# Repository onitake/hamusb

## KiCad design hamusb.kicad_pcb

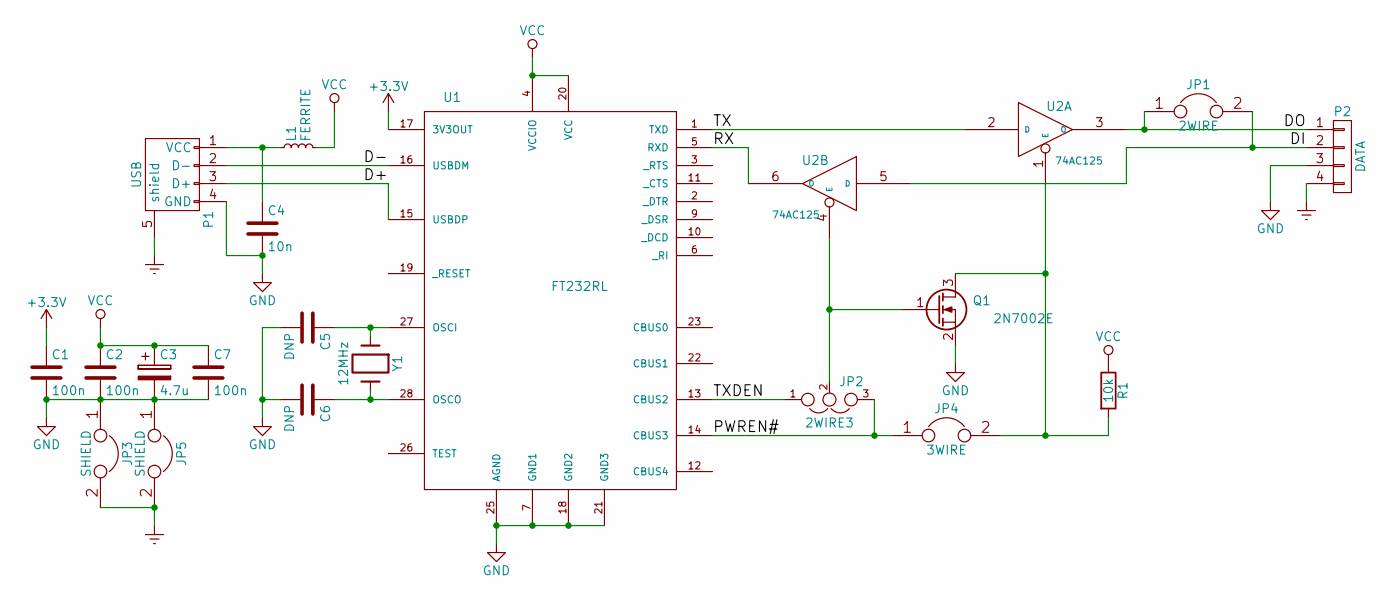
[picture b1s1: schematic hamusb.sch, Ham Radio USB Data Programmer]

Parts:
C1, C2, C7: 100n; C_0805_HandSoldering
C3: 4.7u; c_elec_3x5.3
C4: 10n; C_0805_HandSoldering
C5, C6: DNP; C_0805_HandSoldering
JP1: 2WIRE; Jumper_SMD_2Pin
JP2: 2WIRE3; Jumper_SMD_3Pin
JP3, JP5: SHIELD; Jumper_SMD_2Pin
JP4: 3WIRE; Jumper_SMD_2Pin
L1: FERRITE; R_0805_HandSoldering
P1: USB; USB_A_M
P2: DATA; Pin_Header_Straight_1x04
Q1: 2N7002E; SOT-23_Handsoldering
R1: 10k; R_0805_HandSoldering
U1: FT232RL; SSOP-28_5.3x10.2mm_Pitch0.65mm
U2: 74AC125; TSSOP-14_4.4x5mm_Pitch0.65mm
Y1: 12MHz; Q_49U3HMS

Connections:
+3V3: C1.1, U1.17 (3V3OUT)
/D+: P1.3 (D+), U1.15 (USBDP)
/D-: P1.2 (D-), U1.16 (USBDM)
/DI: JP1.2, P2.2, U2.5 (D)
/DO: JP1.1, P2.1, U2.3 (O)
/PWREN#: JP2.3, JP4.1, U1.14 (CBUS3)
/RX: U1.5 (RXD), U2.6 (O)
/TX: U1.1 (TXD), U2.2 (D)
/TXDEN: JP2.1, U1.13 (CBUS2)
Earth: JP3.2, JP5.2, P1.5 (shield), P2.4
GND: C1.2, C2.2, C3.2, C4.2, C5.2, C6.2, C7.2, JP3.1, JP5.1, P1.4 (GND), P2.3, Q1.2 (S), U1.7 (GND1), U1.18 (GND2), U1.21 (GND3), U1.25 (AGND), U2.7 (GND)
unnamed: C4.1, L1.1, P1.1 (VCC)
unnamed: C5.1, U1.27 (OSCI), Y1.1
unnamed: C6.1, U1.28 (OSCO), Y1.2
unnamed: JP2.2, Q1.1 (G), U2.4 (E)
unnamed: JP4.2, Q1.3 (D), R1.2, U2.1 (E)
VCC: C2.1, C3.1, C7.1, L1.2, R1.1, U1.4 (VCCIO), U1.20 (VCC), U2.14 (VCC)

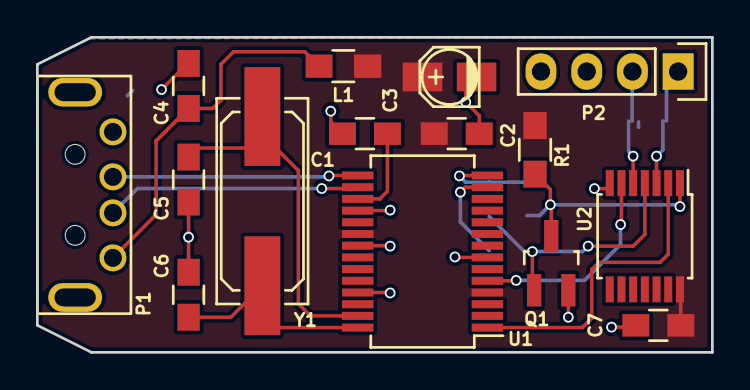
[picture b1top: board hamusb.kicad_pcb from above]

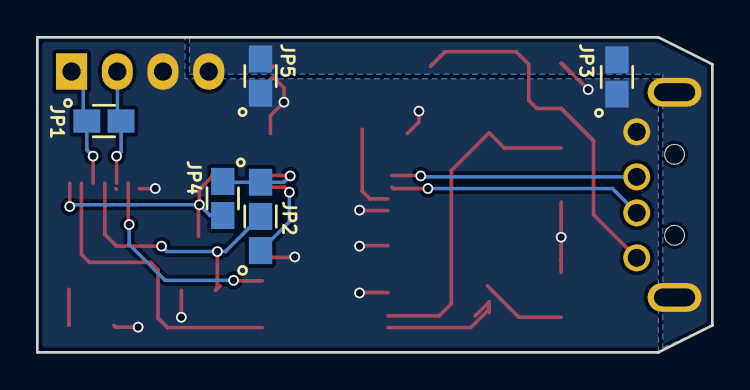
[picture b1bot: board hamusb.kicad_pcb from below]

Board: 2 copper layers, 37.5 x 17.5 mm, 20 parts (5 on the bottom side), 17 nets.

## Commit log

2015-10-16 Initial commit FT232R USB-Serial converter 74AC three-state output drivers TX/RX half-duplex interlock Output configurable for half- or full-duplex mode
2015-10-26 Added data sheet URL for USB plug
2015-10-26 Replaced USB receptable with USB plug
2015-10-26 Added reconstructed circuit schematic from 3rd party data cable (for reference)
2015-10-26 Updated work sheet labels, bumped version
2015-10-27 Cleanup, swapped logic gates, reordered input power circuit
2015-10-27 Added additional net labels Increased shield copper area
2015-10-28 Simplified shield plane Minor placement cleanups

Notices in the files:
hamusb.kicad_pcb:
© 2015 Gregor Riepl
Licensed under the CERN OHL v1.2
